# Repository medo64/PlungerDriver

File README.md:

## PlungerDriver

Small motor driver intended for mounting on syringe in order to push solder or
flux paste out,

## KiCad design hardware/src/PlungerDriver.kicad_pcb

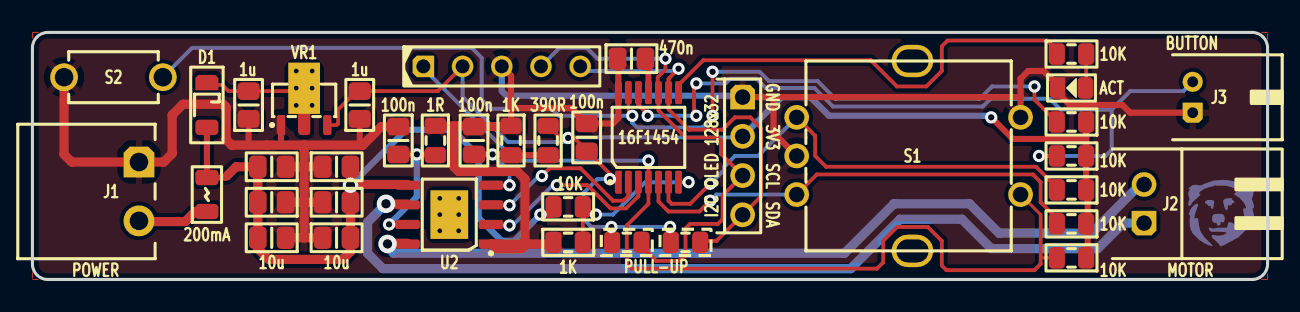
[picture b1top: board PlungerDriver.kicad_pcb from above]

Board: 2 copper layers, 80.0 x 16.0 mm, 39 parts (1 on the bottom side), 22 nets.

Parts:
C1, C2, C3: 100n; C (0805)
C4: 470n; C (0805)
C5, C6: 1u; C (0805)
C7, C8, C9, C10, C11, C12: 10u; C (0805)
D1: B260S1F; D Shottky (SOD123F)
DS1: ACT; DS (0805)
DS2: I2C OLED 128x32; DS OLED 128x32 I2C (4w)
F1: 200mA; F (0805)
ICON: Medo64; ICON Medo64
ICSP: Microchip PIC; ICSP PIC Pogo (5w)
J1: MC 1,5/2; J Phoenix MC (2w)
J2: locked; J JST XH S (2w)
J3: S2B-PH; J JST PH S (2w)
R1: 1R; R (0805)
R2: 390R; R (0805)
R3, R4: 1K; R (0805)
R5, R6, R7, R8, R9, R10, R11: 10K; R (0805)
R12, R13: 5K1; R Optional (0805)
S1: Rotary; S Rotary Switch (5w)
S2: SPST; S Tactile SPST-NO 12V 50mA 6.0x3.5x5.0mm (2w)
U1: 16F1454; U Micro PIC16F1454 (TSSOP-14)
U2: TB67H450AFNG; U Driver Motor TB67H450AFNG' (SOIC-8)
VR1: AS78L05RTR; VR Linear AP7380-33Y' (SOT89-3)

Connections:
3V3: C1.2, C6.2, DS2.2, ICSP.2, R2.1, R6.1, R7.1, R8.1, R9.1, R10.1, R12.2, R13.2, U1.1, VR1.3
5V: C5.2, D1.1, VR1.2
6V: C7.2, C8.2, C9.2, C10.2, C11.2, C12.2, D1.2, F1.2, R11.2, U2.5
DRIVER_IN1: U1.2, U2.3
DRIVER_IN2: U1.3, U2.2
DRIVER_OUT1: J2.1, U2.6
DRIVER_OUT2: J2.2, U2.8
DRIVER_RS: C3.2, R1.2, U2.7
DRIVER_VREF: C2.2, R2.2, R3.2, U2.4
GND: C1.1, C2.1, C3.1, C4.1, C5.1, C6.1, C7.1, C8.1, C9.1, C10.1, C11.1, C12.1, DS1.1, DS2.1, ICSP.3, J1.1, J3.1, R1.1, R3.1, R4.1, S1.1, S1.C, S2.1, U1.14, U2.1, VR1.1
IN_ADC_INPUT_VOLTAGE: R4.2, R11.1, U1.7
IN_EXTERNAL_SWITCH: J3.2, R7.2, U1.12
IN_INTERNAL_SWITCH: R6.2, S2.2, U1.13
IN_ROTARY_A: R8.2, S1.A, U1.6
IN_ROTARY_B: R9.2, S1.B, U1.5
IN_ROTARY_SWITCH: ICSP.1, R10.2, S1.2, U1.4
LED_ACT: R5.1, U1.8
LED_ACT': DS1.2, R5.2
OLED_SCL: DS2.3, ICSP.4, R12.1, U1.10
OLED_SDA: DS2.4, ICSP.5, R13.1, U1.9
Vbus: C4.2, U1.11
Vin: F1.1, J1.2

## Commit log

2023-09-05 Refactored a bit
2023-09-05 Added external switch input
2023-09-05 Changed external switch to JST PH
2023-09-05 Moved connectors a bit
2023-09-05 Added internal switch
2023-09-05 Added parts
2023-09-05 Added motor
2023-09-06 Refactored to remove pulllup/input from rotary switch C line
2023-09-06 Updated silkscreen
2023-09-07 Added voltage divider input
2023-09-12 Swapped I2C/SPI lines + general footprint update
2023-09-12 Refactoring board a bit more
2023-09-12 Added I2C pullup resistors
2023-09-12 Moving resistors a bit
2023-09-13 Refacored I2C pull up resistors
2023-09-19 Added icon and title
2023-10-10 Added initial firmware
2023-10-11 Refactoring rotary switch support
2023-10-11 Increased I2C frequency
2023-10-11 Increased LED resistor value
2023-10-11 rotary: added _SSD1306_DISPLAY_FLIP
2023-10-11 Refactoring I2C master a bit
2023-10-11 Refactoring SSD1306 OLED writes
2023-10-11 ssd1306: Added high and low character support
2023-10-12 Added button support
2023-10-12 Refactoring
2023-10-12 rotary: working with PEC12R
2023-10-12 rotary: better filtering
2023-10-12 ticker: refactored
2023-10-12 Minor update
2023-10-13 Added basic menu
2023-10-13 Added motor control
2023-10-14 Fixed missing Vref divider resistor (doh!)
2023-10-14 ssd1306: added internal i2c support
2023-10-14 rotary: removed unused rotary defines
2023-10-14 Refactored button handling
2023-10-16 Basic drive
2023-11-19 Updated parts
2023-11-21 Added settings
2023-11-21 Added profile configuration
2023-11-26 Fixed reversing when flipped
2023-11-26 Updated settings
2023-11-26 Added readme
2023-12-04 Updated motor to 300rpm
2024-09-02 Refactoring OLED class
